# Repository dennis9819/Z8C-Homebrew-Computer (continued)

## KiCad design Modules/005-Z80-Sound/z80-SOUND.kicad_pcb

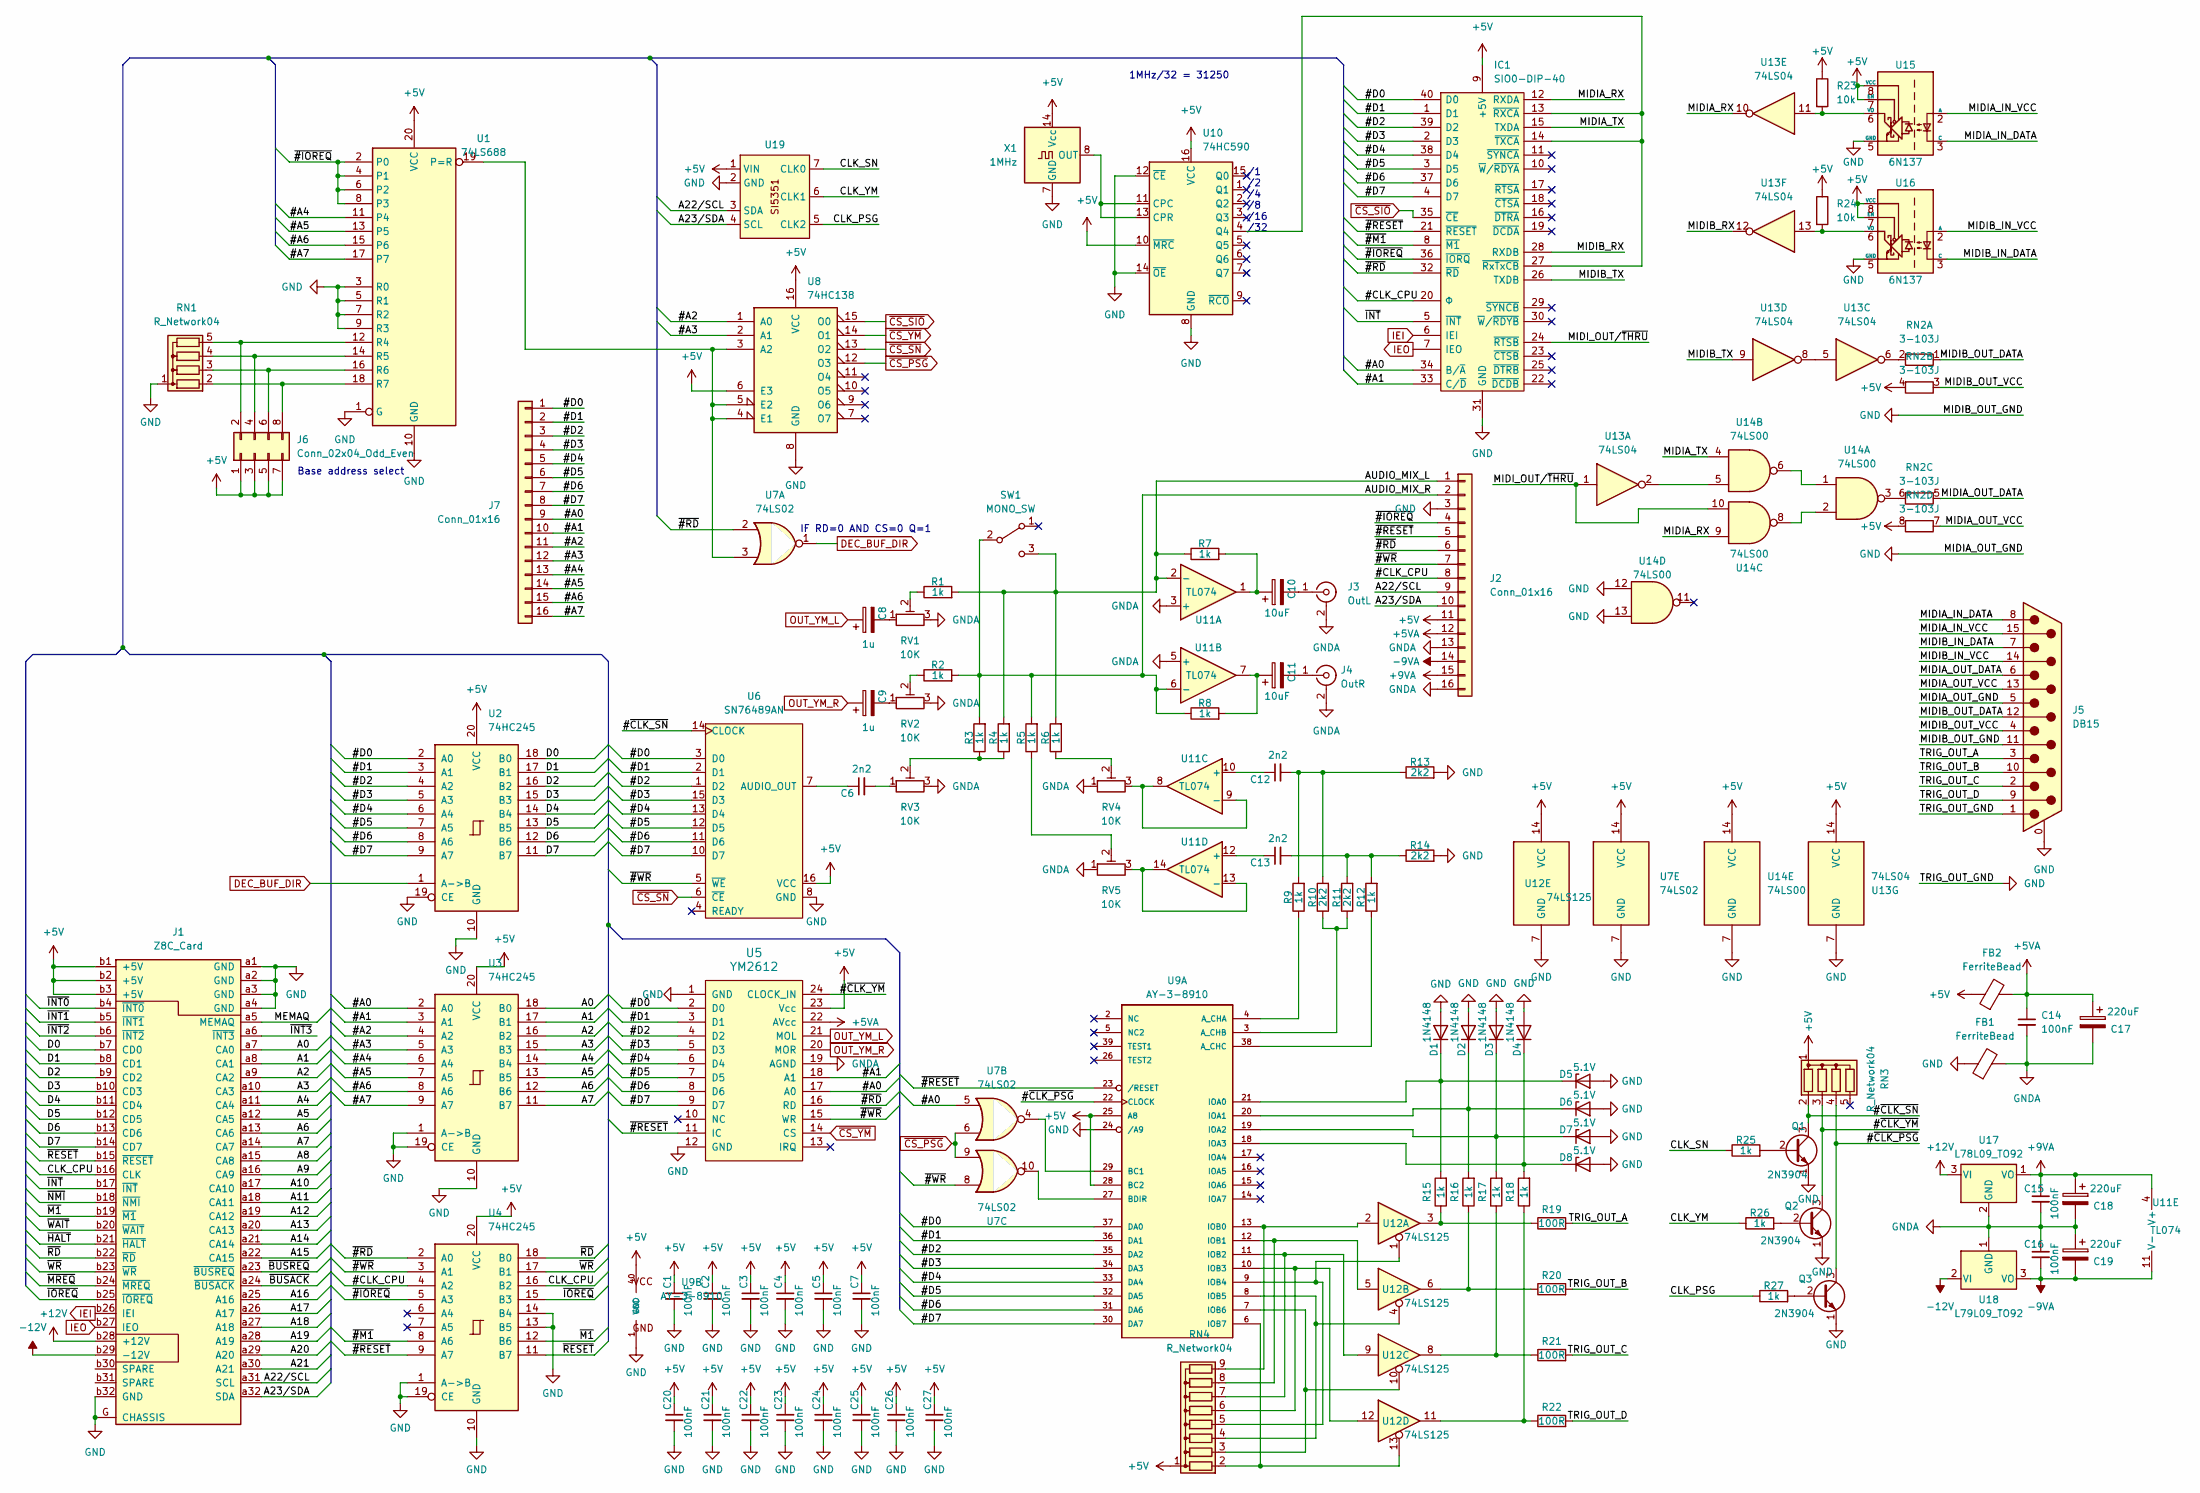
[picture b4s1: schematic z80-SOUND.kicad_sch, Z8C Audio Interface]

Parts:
C1, C2, C3, C4, C5, C7, C14, C15, C16, C20, C21, C22, C23, C24, C25, C26, C27: 100nF; C_Rect_L7.0mm_W2.0mm_P5.00mm
C6, C12, C13: 2n2; C_Rect_L7.0mm_W2.0mm_P5.00mm
C8, C9: 1u; CP_Radial_D6.3mm_P2.50mm
C10, C11: 10uF; CP_Radial_D6.3mm_P2.50mm
C17, C18, C19: 220uF; CP_Radial_D8.0mm_P3.50mm
D1, D2, D3, D4: 1N4148; D_DO-35_SOD27_P7.62mm_Horizontal
D5, D6, D7, D8: 5.1V; D_DO-34_SOD68_P7.62mm_Horizontal
FB1, FB2: FerriteBead; R_Axial_DIN0414_L11.9mm_D4.5mm_P15.24mm_Horizontal
IC1: SIO0-DIP-40; DIP-40_W15.24mm_Socket; Manufacturer_Part_Number Z84C4206PEG; Mouser Part Number 692-Z84C4206PEG
J1: Z8C_Card; Z8C Card
J2, J7: Conn_01x16; PinSocket_1x16_P2.54mm_Vertical
J3: OutL; RCA_Reichelt
J4: OutR; RCA_Reichelt
J5: DB15; DSUB-15_Female_Horizontal_P2.77x2.84mm_EdgePinOffset9.90mm_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
J6: Conn_02x04_Odd_Even; PinHeader_2x04_P2.54mm_Vertical
Q1, Q2, Q3: 2N3904; TO-92_Inline
R1, R2, R3, R4, R5, R6, R7, R8, R9, R12, R15, R16, R17, R18, R25, R26, R27: 1k; R_Axial_DIN0204_L3.6mm_D1.6mm_P7.62mm_Horizontal
R10, R11, R13, R14: 2k2; R_Axial_DIN0204_L3.6mm_D1.6mm_P7.62mm_Horizontal
R19, R20, R21, R22: 100R; R_Axial_DIN0204_L3.6mm_D1.6mm_P7.62mm_Horizontal
R23, R24: 10k; R_Axial_DIN0204_L3.6mm_D1.6mm_P7.62mm_Horizontal
RN1, RN3: R_Network04; R_Array_SIP5
RN2: 3-103J; R_Array_SIP8
RN4: R_Network04; R_Array_SIP9
RV1, RV2, RV3, RV4, RV5: 10K; Potentiometer_Bourns_3299W_Vertical
SW1: MONO_SW; DPDT_Vertical
U1: 74LS688; DIP-20_W7.62mm_Socket_LongPads
U2, U3, U4: 74HC245; DIP-20_W7.62mm_Socket_LongPads
U5: YM2612; DIP-24_W15.24mm_Socket
U6: SN76489AN; DIP-16_W7.62mm_Socket
U7: 74LS02; DIP-14_W7.62mm_Socket
U8: 74HC138; DIP-16_W7.62mm_Socket_LongPads
U9: AY-3-8910; DIP-40_W15.24mm_Socket
U10: 74HC590; DIP-16_W7.62mm_Socket_LongPads
U11: TL074; DIP-14_W7.62mm_Socket
U12: 74LS125; DIP-14_W7.62mm_Socket
U13: 74LS04; DIP-14_W7.62mm_Socket
U14: 74LS00; DIP-14_W7.62mm_Socket
U15, U16: 6N137; DIP-8_W7.62mm
U17: L78L09_TO92; TO-92_Inline
U18: L79L09_TO92; TO-92_Inline
U19: PinSocket_1x07_P2.54mm_Vertical
X1: 1MHz; Oscillator_DIP-14

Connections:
+5V: C1.1, C2.1, C3.1, C4.1, C5.1, C7.1, C20.1, C21.1, C22.1, C23.1, C24.1, C25.1, C26.1, C27.1, FB2.1, IC1.9 (+5V), J1.b1 (+5V), J1.b2 (+5V), J1.b3 (+5V), J2.11, J6.1, J6.3, J6.5, J6.7, R23.1, R24.1, RN2.4 (R2.2), RN2.8 (R4.2), RN3.1 (common), RN4.1 (common), U1.20 (VCC), U2.20 (VCC), U3.20 (VCC), U4.20 (VCC), U5.23 (Vcc), U6.16 (VCC), U7.14 (VCC), U8.6 (E3), U8.16 (VCC), U9.25 (A8), U9.28 (BC2), U9.40 (VCC), U10.10 (~MRC), U10.16 (VCC), U12.14 (VCC), U13.14 (VCC), U14.14 (VCC), U15.7 (EN), U15.8 (VCC), U16.7 (EN), U16.8 (VCC), U19.1 (VIN), X1.14 (Vcc)
+5VA: C14.1, C17.1, FB2.2, J2.12, U5.22 (AVcc)
+9VA: C15.1, C18.1, J2.15, U11.4 (V+), U17.1 (VO)
+12V: J1.b28 (+12V), U17.3 (VI)
-9VA: C16.2, C19.2, J2.14, U11.11 (V-), U18.3 (VO)
-12V: J1.b29 (-12V), U18.2 (VI)
/#A0: IC1.34 (B/~A), J7.9, U3.2 (A0), U5.17 (A0), U7.5
/#A1: IC1.33 (C/~D), J7.10, U3.3 (A1), U5.18 (A1)
/#A2: J7.11, U3.4 (A2), U8.1 (A0)
/#A3: J7.12, U3.5 (A3), U8.2 (A1)
/#A4: J7.13, U1.11 (P4), U3.6 (A4)
/#A5: J7.14, U1.13 (P5), U3.7 (A5)
/#A6: J7.15, U1.15 (P6), U3.8 (A6)
/#A7: J7.16, U1.17 (P7), U3.9 (A7)
/#CLK_CPU: IC1.20 (Φ), J2.8, U4.4 (A2)
/#D0: IC1.40 (D0), J7.1, U2.2 (A0), U5.2 (D0), U6.3 (D0), U9.37 (DA0)
/#D1: IC1.1 (D1), J7.2, U2.3 (A1), U5.3 (D1), U6.2 (D1), U9.36 (DA1)
/#D2: IC1.39 (D2), J7.3, U2.4 (A2), U5.4 (D2), U6.1 (D2), U9.35 (DA2)
/#D3: IC1.2 (D3), J7.4, U2.5 (A3), U5.5 (D3), U6.15 (D3), U9.34 (DA3)
/#D4: IC1.38 (D4), J7.5, U2.6 (A4), U5.6 (D4), U6.13 (D4), U9.33 (DA4)
/#D5: IC1.3 (D5), J7.6, U2.7 (A5), U5.7 (D5), U6.12 (D5), U9.32 (DA5)
/#D6: IC1.37 (D6), J7.7, U2.8 (A6), U5.8 (D6), U6.11 (D6), U9.31 (DA6)
/#D7: IC1.4 (D7), J7.8, U2.9 (A7), U5.9 (D7), U6.10 (D7), U9.30 (DA7)
/#~CLK_PSG: Q3.3 (C), RN3.4 (R3), U9.22 (CLOCK)
/#~CLK_SN: Q1.3 (C), RN3.2 (R1), U6.14 (CLOCK)
/#~CLK_YM: Q2.3 (C), RN3.3 (R2), U5.24 (CLOCK_IN)
/A0: J1.a7 (CA0), U3.18 (B0)
/A1: J1.a8 (CA1), U3.17 (B1)
/A2: J1.a9 (CA2), U3.16 (B2)
/A3: J1.a10 (CA3), U3.15 (B3)
/A4: J1.a11 (CA4), U3.14 (B4)
/A5: J1.a12 (CA5), U3.13 (B5)
/A6: J1.a13 (CA6), U3.12 (B6)
/A7: J1.a14 (CA7), U3.11 (B7)
/A8: J1.a15 (CA8)
/A9: J1.a16 (CA9)
/A10: J1.a17 (CA10)
/A11: J1.a18 (CA11)
/A12: J1.a19 (CA12)
/A13: J1.a20 (CA13)
/A14: J1.a21 (CA14)
/A15: J1.a22 (CA15)
/A16: J1.a25 (A16)
/A17: J1.a26 (A17)
/A18: J1.a27 (A18)
/A19: J1.a28 (A19)
/A20: J1.a29 (A20)
/A21: J1.a30 (A21)
/A22/SCL: J1.a31 (SCL), J2.9, U19.3 (SDA)
/A23/SDA: J1.a32 (SDA), J2.10, U19.4 (SCL)
/AUDIO_MIX_L: J2.1, R1.2, R4.2, R6.2, R7.1, SW1.3 (C), U11.2 (-)
/AUDIO_MIX_R: J2.2, R2.2, R3.2, R5.2, R8.1, SW1.2 (B), U11.6 (-)
/CLK_CPU: J1.b16 (CLK), U4.16 (B2)
/CLK_PSG: R27.1, U19.5 (CLK2)
/CLK_SN: R25.1, U19.7 (CLK0)
/CLK_YM: R26.1, U19.6 (CLK1)
/D0: J1.b7 (CD0), U2.18 (B0)
/D1: J1.b8 (CD1), U2.17 (B1)
/D2: J1.b9 (CD2), U2.16 (B2)
/D3: J1.b10 (CD3), U2.15 (B3)
/D4: J1.b11 (CD4), U2.14 (B4)
/D5: J1.b12 (CD5), U2.13 (B5)
/D6: J1.b13 (CD6), U2.12 (B6)
/D7: J1.b14 (CD7), U2.11 (B7)
/MEMAQ: J1.a5 (MEMAQ)
/MIDIA_IN_DATA: J5.8, U15.3 (C)
/MIDIA_IN_VCC: J5.15, U15.2 (A)
/MIDIA_OUT_DATA: J5.6, RN2.5 (R3.1)
/MIDIA_OUT_VCC: J5.13, RN2.7 (R4.1)
/MIDIA_RX: IC1.12 (RXDA), U13.10, U14.9
/MIDIA_TX: IC1.15 (TXDA), U14.4
/MIDIB_IN_DATA: J5.7, U16.3 (C)
/MIDIB_IN_VCC: J5.14, U16.2 (A)
/MIDIB_OUT_DATA: J5.12, RN2.1 (R1.1)
/MIDIB_OUT_VCC: J5.4, RN2.3 (R2.1)
/MIDIB_RX: IC1.28 (RXDB), U13.12
/MIDIB_TX: IC1.26 (TXDB), U13.9
/MIDI_OUT/~THRU: IC1.24 (~RTSB), U13.1, U14.10
/TRIG_OUT_A: J5.3, R19.2
/TRIG_OUT_B: J5.10, R20.2
/TRIG_OUT_C: J5.2, R21.2
/TRIG_OUT_D: J5.9, R22.2
/~#IOREQ: IC1.36 (~IORQ), J2.4, U1.2 (P0), U1.4 (P1), U1.6 (P2), U1.8 (P3), U4.5 (A3)
/~#M1: IC1.8 (~M1), U4.8 (A6)
/~#RD: IC1.32 (~RD), J2.6, U4.2 (A0), U5.16 (RD), U7.2
/~#RESET: IC1.21 (~RESET), J2.5, U4.9 (A7), U5.11 (IC), U9.23 (/RESET)
/~#WR: J2.7, U4.3 (A1), U5.15 (WR), U6.5 (~WE), U7.8
/~BUSACK: J1.a24 (~BUSACK)
/~BUSREQ: J1.a23 (~BUSREQ)
/~HALT: J1.b21 (~HALT)
/~INT0: J1.b4 (~INT0)
/~INT1: J1.b5 (~INT1)
/~INT2: J1.b6 (~INT2)
/~INT3: J1.a6 (~INT3)
/~INT: IC1.5 (~INT), J1.b17 (~INT)
/~IOREQ: J1.b25 (~IOREQ), U4.15 (B3)
/~M1: J1.b19 (~M1), U4.12 (B6)
/~MREQ: J1.b24 (~MREQ)
/~NMI: J1.b18 (~NMI)
/~RD: J1.b22 (~RD), U4.18 (B0)
/~RESET: J1.b15 (~RESET), U4.11 (B7)
/~WAIT: J1.b20 (~WAIT)
/~WR: J1.b23 (~WR), U4.17 (B1)
DEC_BUF_DIR: U2.1 (A->B), U7.1
GND: C1.2, C2.2, C3.2, C4.2, C5.2, C7.2, C20.2, C21.2, C22.2, C23.2, C24.2, C25.2, C26.2, C27.2, D1.2 (A), D2.2 (A), D3.2 (A), D4.2 (A), D5.2 (A), D6.2 (A), D7.2 (A), D8.2 (A), FB1.1, IC1.31 (GND), J1.G (CHASSIS), J1.a1 (GND), J1.a2 (GND), J1.a3 (GND), J1.a4 (GND), J1.b32 (GND), J2.3, J5.0 (PAD), J5.1, J5.5, J5.11 (P111), Q1.1 (E), Q2.1 (E), Q3.1 (E), R13.2, R14.2, RN1.1 (common), U1.1 (G), U1.3 (R0), U1.5 (R1), U1.7 (R2), U1.9 (R3), U1.10 (GND), U2.10 (GND), U2.19 (CE), U3.1 (A->B), U3.10 (GND), U3.19 (CE), U4.1 (A->B), U4.10 (GND), U4.13 (B5), U4.14 (B4), U4.19 (CE), U5.1 (GND), U5.12 (GND), U6.8 (GND), U7.7 (GND), U8.8 (GND), U9.1 (GND), U9.24 (/A9), U10.8 (GND), U10.12 (~CE), U10.14 (~OE), U12.7 (GND), U13.7 (GND), U14.7 (GND), U14.12, U14.13, U15.5 (GND), U16.5 (GND), U19.2 (GND), X1.7 (GND)
GNDA: C14.2, C15.2, C16.1, C17.2, C18.2, C19.1, FB1.2, J2.13, J2.16, J3.2 (Ext), J4.2 (Ext), RV1.3, RV2.3, RV3.3, RV4.1, RV5.1, U5.19 (AGND), U11.3 (+), U11.5 (+), U17.2 (GND), U18.1 (GND)
IEI: IC1.6 (IEI), J1.b26 (IEI)
IEO: IC1.7 (IEO), J1.b27 (IEO)
unnamed: C6.2, RV3.1
unnamed: C8.2, RV1.1
unnamed: C9.2, RV2.1
unnamed: C10.1, R7.2, U11.1
unnamed: C11.1, R8.2, U11.7
unnamed: C12.2, R9.2, R10.2, R13.1
unnamed: C13.2, R11.2, R12.2, R14.1
unnamed: D1.1 (K), D5.1 (K), R15.2, U9.21 (IOA0)
unnamed: D2.1 (K), D6.1 (K), R16.2, U9.20 (IOA1)
unnamed: D3.1 (K), D7.1 (K), R17.2, U9.19 (IOA2)
unnamed: D4.1 (K), D8.1 (K), R18.2, U9.18 (IOA3)
unnamed: IC1.13 (~RXCA), IC1.14 (~TXCA), IC1.27 (~RxTxCB), U10.4 (Q4)
unnamed: C10.2, J3.1 (In)
unnamed: C11.2, J4.1 (In)
unnamed: J6.2, RN1.5 (R4), U1.12 (R4)
unnamed: J6.4, RN1.4 (R3), U1.14 (R5)
unnamed: J6.6, RN1.3 (R2), U1.16 (R6)
unnamed: J6.8, RN1.2 (R1), U1.18 (R7)
unnamed: Q1.2 (B), R25.2
unnamed: Q2.2 (B), R26.2
unnamed: Q3.2 (B), R27.2
unnamed: R1.1, RV1.2
unnamed: R2.1, RV2.2
unnamed: R3.1, R4.1, RV3.2
unnamed: R5.1, RV5.2
unnamed: R6.1, RV4.2
unnamed: R15.1, R19.1, U12.3
unnamed: R16.1, R20.1, U12.6
unnamed: R17.1, R21.1, U12.8
unnamed: R18.1, R22.1, U12.11
unnamed: RN2.2 (R1.2), U13.6
unnamed: RN2.6 (R3.2), U14.3
unnamed: RN4.2 (R1), U9.6 (IOB7), U12.13
unnamed: RN4.3 (R2), U9.7 (IOB6), U12.10
unnamed: RN4.4 (R3), U9.8 (IOB5), U12.4
unnamed: RN4.5 (R4), U9.9 (IOB4), U12.1
unnamed: RN4.6 (R5), U9.10 (IOB3), U12.12
unnamed: RN4.7 (R6), U9.11 (IOB2), U12.9
unnamed: RN4.8 (R7), U9.12 (IOB1), U12.5
unnamed: RN4.9 (R8), U9.13 (IOB0), U12.2
unnamed: U1.19 (P=R), U7.3, U8.3 (A2), U8.4 (E1), U8.5 (E2)
unnamed: C6.1, U6.7 (AUDIO_OUT)
unnamed: R9.1, U9.4 (A_CHA)
unnamed: R10.1, R11.1, U9.3 (A_CHB)
unnamed: R12.1, U9.38 (A_CHC)
unnamed: U7.4, U9.29 (BC1)
unnamed: U7.10, U9.27 (BDIR)
unnamed: U10.11 (CPC), U10.13 (CPR), X1.8 (OUT)
unnamed: C12.1, U11.10 (+)
unnamed: RV4.3, U11.8, U11.9 (-)
unnamed: C13.1, U11.12 (+)
unnamed: RV5.3, U11.13 (-), U11.14
unnamed: U13.2, U14.5
unnamed: U13.5, U13.8
unnamed: U14.1, U14.6
unnamed: U14.2, U14.8
unnamed: R23.2, U13.11, U15.6 (VO)
unnamed: R24.2, U13.13, U16.6 (VO)
OUT_YM_L: C8.1, U5.21 (MOL)
OUT_YM_R: C9.1, U5.20 (MOR)
~CS_PSG: U7.6, U7.9, U8.12 (O3)
~CS_SIO: IC1.35 (~CE), U8.15 (O0)
~CS_SN: U6.6 (~CE), U8.13 (O2)
~CS_YM: U5.14 (CS), U8.14 (O1)

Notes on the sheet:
/1 /2 /4 /8 /16 /32
Base address select
IF RD=0 AND CS=0 Q=1
1MHz/32 = 31250

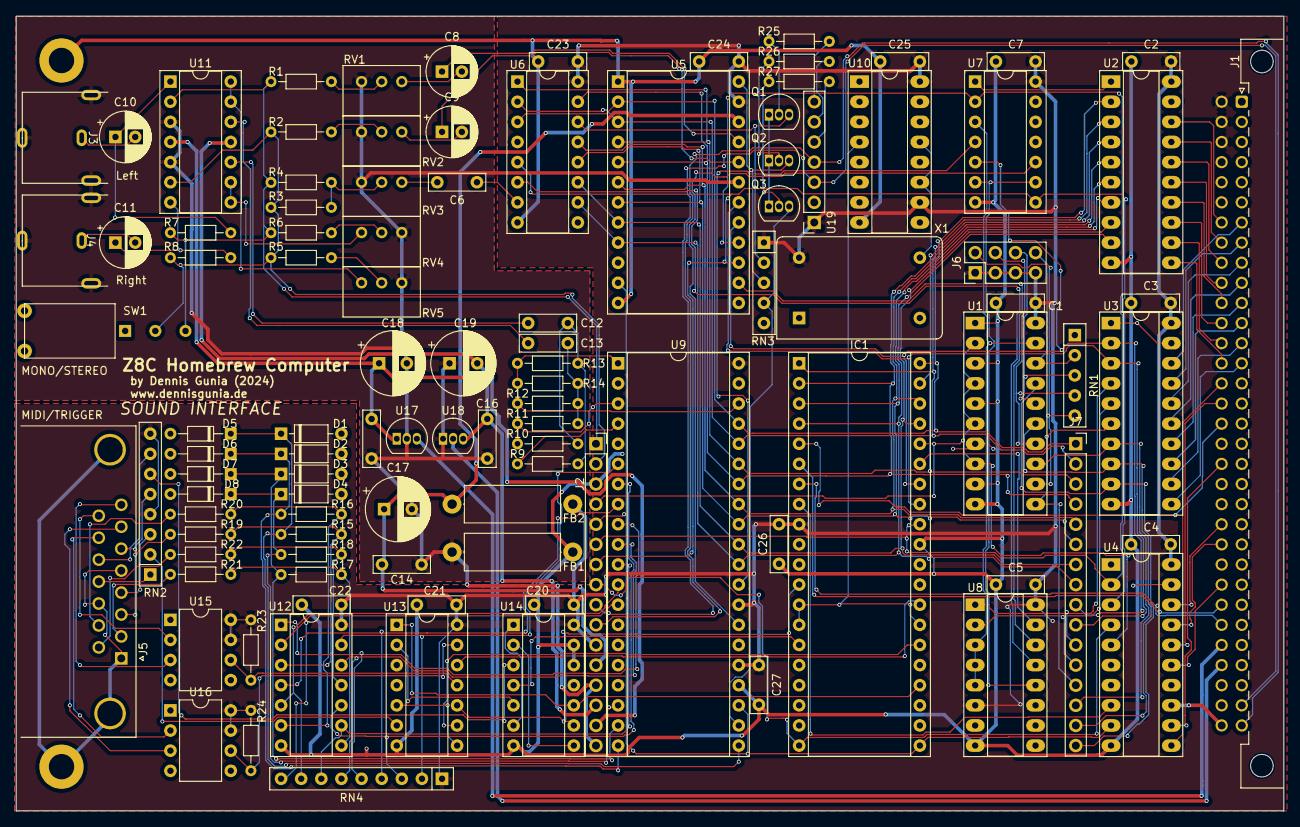
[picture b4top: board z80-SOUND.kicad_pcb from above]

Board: 2 copper layers, 160.0 x 100.3 mm, 105 parts (0 on the bottom side), 147 nets.

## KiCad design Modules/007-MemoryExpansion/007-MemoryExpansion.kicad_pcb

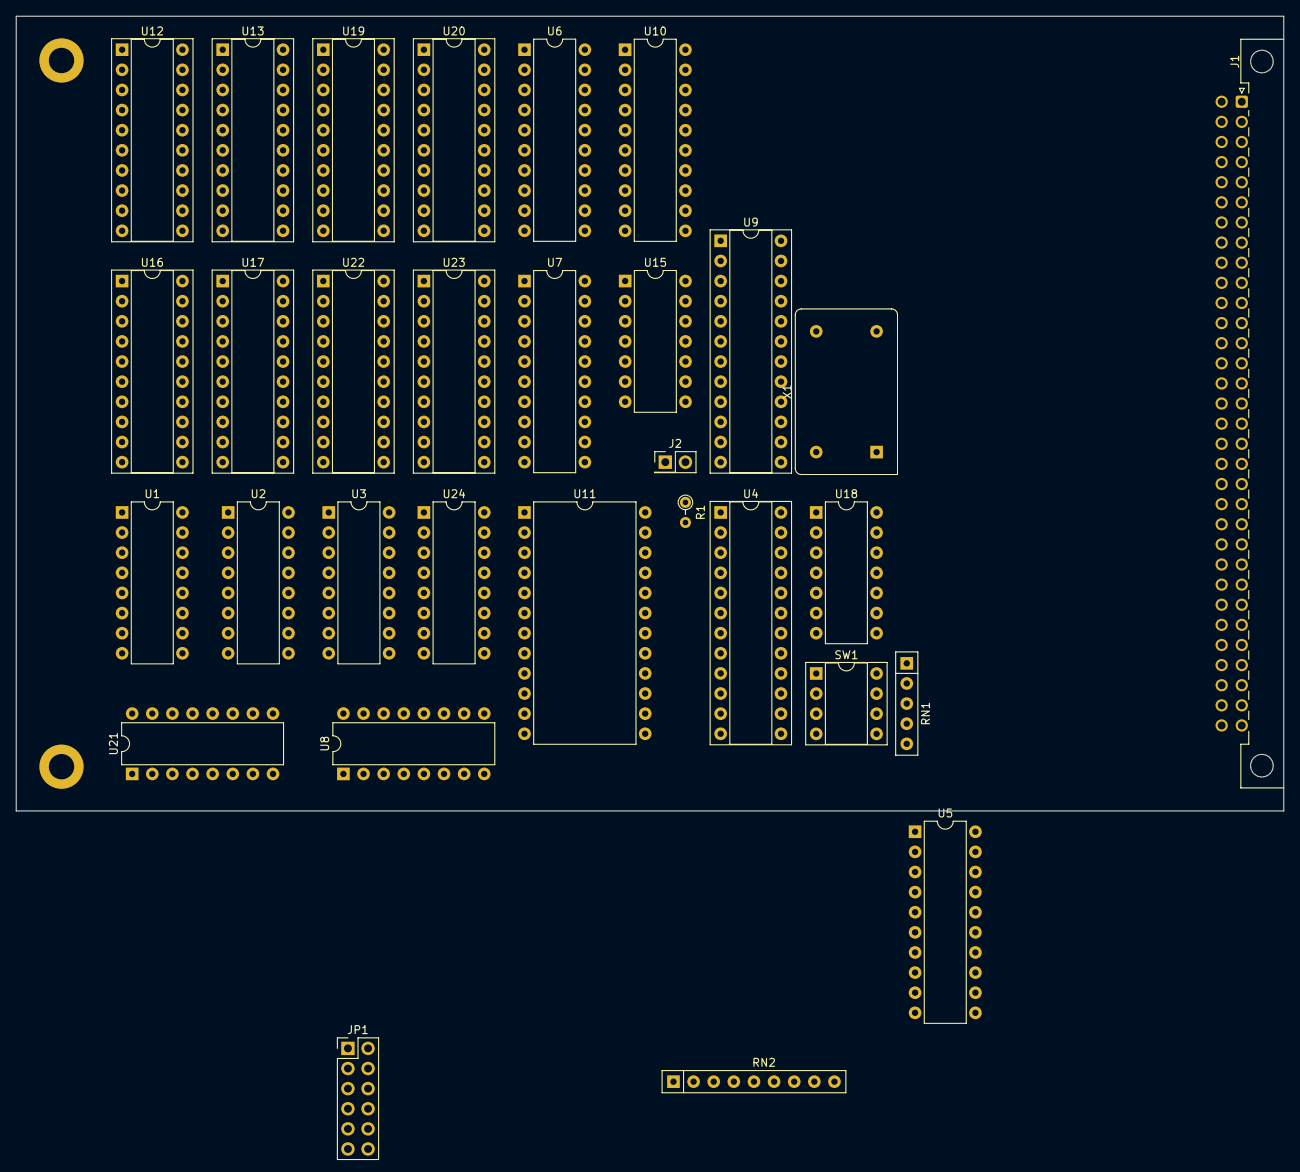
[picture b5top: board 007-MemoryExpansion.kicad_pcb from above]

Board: 2 copper layers, 160.0 x 100.3 mm, 31 parts (0 on the bottom side), 98 nets, no tracks yet.

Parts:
J1: Z8C_Ca#RD; Z8C Card
J2: ENA19; PinHeader_2x01_P2.54mm_Vertical
JP1: Conn_02x06_Odd_Even; PinHeader_2x06_P2.54mm_Vertical
R1: 4.7k; R_Axial_DIN0204_L3.6mm_D1.6mm_P2.54mm_Vertical
RN1: 4k7; R_Array_SIP5
RN2: R_Network08; R_Array_SIP9
SW1: SW_DIP_x04; DIP-8_W7.62mm_Socket
U1, U2, U3, U8: 74LS157; DIP-16_W7.62mm
U4, U9: DIP-24_W7.62mm_Socket
U5: 74LS688; DIP-20_W7.62mm
U6, U10: 74LS245; DIP-20_W7.62mm
U7: 74LS374; DIP-20_W7.62mm
U11: DIP-24_W15.24mm
U12, U13, U16, U17, U19, U20, U22, U23: DIP-20_W7.62mm_Socket
U15: 74LS74; DIP-14_W7.62mm
U18: 74LS125; DIP-14_W7.62mm
U21: 74LS138; DIP-16_W7.62mm
U24: 74LS175; DIP-16_W7.62mm
X1: 40MHz; Oscillator_DIP-14

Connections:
+5V: J1.b1 (+5V), J1.b2 (+5V), J1.b3 (+5V), J2.1, JP1.1, JP1.3, JP1.5, JP1.7, JP1.9, JP1.11, SW1.1, SW1.2, SW1.3, SW1.4, U4.24 (VCC), U5.20 (VCC), U6.20 (VCC), U7.20 (VCC), U8.16 (VCC), U9.24 (VCC), U10.20 (VCC), U11.24 (Vcc), U12.20 (VSS), U13.20 (VSS), U16.20 (VSS), U17.20 (VSS), U19.20 (VSS), U20.20 (VSS), U21.6 (E3), U21.16 (VCC), U22.20 (VSS), U23.20 (VSS), U24.1 (~Mr), U24.16 (VCC), X1.14 (Vcc)
/#CA0: U1.2 (I0a), U4.9 (I9)
/#CA1: U1.5 (I0b), U4.11 (I10)
/#CA2: U1.11 (I0c), U5.6 (P2)
/#CA3: U1.14 (I0d), U5.8 (P3)
/#CA4: U2.2 (I0a), U5.11 (P4)
/#CA5: U2.5 (I0b), U5.13 (P5)
/#CA6: U2.11 (I0c), U5.15 (P6)
/#CA7: U2.14 (I0d), U5.17 (P7)
/#CA15: U4.13 (I13/~OE), U8.13 (I1d)
/#CD0: U6.2 (A0), U7.3 (D0), U10.2 (A0), U18.3, U24.4 (D0)
/#CD1: U6.3 (A1), U7.4 (D1), U10.3 (A1), U24.5 (D1)
/#CD2: U6.4 (A2), U7.7 (D2), U10.4 (A2), U24.12 (D2)
/#CD3: U6.5 (A3), U7.8 (D3), U10.5 (A3), U24.13 (D3)
/#CD4: U6.6 (A4), U7.13 (D4), U10.6 (A4)
/#CD5: U6.7 (A5), U7.14 (D5), U10.7 (A5)
/#CD6: U6.8 (A6), U7.17 (D6), U10.8 (A6)
/#CD7: U6.9 (A7), U7.18 (D7), U10.9 (A7)
/JENA19: J2.2, R1.1, U18.2
/MBA12: U1.13 (I1d), U10.18 (B0), U11.9 (D0)
/MBA13: U2.3 (I1a), U10.17 (B1), U11.10 (D1)
/MBA14: U2.6 (I1b), U10.16 (B2), U11.11 (D2)
/MBA15: U2.10 (I1c), U10.15 (B3), U11.13 (D3)
/MBA16: U2.13 (I1d), U10.14 (B4), U11.14 (D4)
/MBA17: U3.3 (I1a), U10.13 (B5), U11.15 (D5)
/MBA18: U10.12 (B6), U11.16 (D6), U21.1 (A0)
/MBPROT: U4.16 (IO16), U10.11 (B7), U11.17 (D7)
/MDA0: U6.18 (B0), U12.1 (DQ0), U13.1 (DQ0), U19.1 (DQ0), U20.1 (DQ0)
/MDA1: U6.17 (B1), U12.2 (DQ1), U13.2 (DQ1), U19.2 (DQ1), U20.2 (DQ1)
/MDA2: U6.16 (B2), U12.18 (DQ2), U13.18 (DQ2), U19.18 (DQ2), U20.18 (DQ2)
/MDA3: U6.15 (B3), U12.19 (DQ3), U13.19 (DQ3), U19.19 (DQ3), U20.19 (DQ3)
/MDA4: U6.14 (B4), U16.1 (DQ0), U17.1 (DQ0), U22.1 (DQ0), U23.1 (DQ0)
/MDA5: U6.13 (B5), U16.2 (DQ1), U17.2 (DQ1), U22.2 (DQ1), U23.2 (DQ1)
/MDA6: U6.12 (B6), U16.18 (DQ2), U17.18 (DQ2), U22.18 (DQ2), U23.18 (DQ2)
/MDA7: U6.11 (B7), U16.19 (DQ3), U17.19 (DQ3), U22.19 (DQ3), U23.19 (DQ3)
/MMA0: U1.4 (Za), U12.6 (A0), U13.6 (A0), U16.6 (A0), U17.6 (A0), U19.6 (A0), U20.6 (A0), U22.6 (A0), U23.6 (A0)
/MMA1: U1.7 (Zb), U12.7 (A1), U13.7 (A1), U16.7 (A1), U17.7 (A1), U19.7 (A1), U20.7 (A1), U22.7 (A1), U23.7 (A1)
/MMA2: U1.9 (Zc), U12.8 (A2), U13.8 (A2), U16.8 (A2), U17.8 (A2), U19.8 (A2), U20.8 (A2), U22.8 (A2), U23.8 (A2)
/MMA3: U1.12 (Zd), U12.9 (A3), U13.9 (A3), U16.9 (A3), U17.9 (A3), U19.9 (A3), U20.9 (A3), U22.9 (A3), U23.9 (A3)
/MMA4: U2.4 (Za), U12.11 (A4), U13.11 (A4), U16.11 (A4), U17.11 (A4), U19.11 (A4), U20.11 (A4), U22.11 (A4), U23.11 (A4)
/MMA5: U2.7 (Zb), U12.12 (A5), U13.12 (A5), U16.12 (A5), U17.12 (A5), U19.12 (A5), U20.12 (A5), U22.12 (A5), U23.12 (A5)
/MMA6: U2.9 (Zc), U12.13 (A6), U13.13 (A6), U16.13 (A6), U17.13 (A6), U19.13 (A6), U20.13 (A6), U22.13 (A6), U23.13 (A6)
/MMA7: U2.12 (Zd), U12.14 (A7), U13.14 (A7), U16.14 (A7), U17.14 (A7), U19.14 (A7), U20.14 (A7), U22.14 (A7), U23.14 (A7)
/MMA8: U3.4 (Za), U12.15 (A8), U13.15 (A8), U16.15 (A8), U17.15 (A8), U19.15 (A8), U20.15 (A8), U22.15 (A8), U23.15 (A8)
/MPROTEN: U4.15 (IO15), U7.19 (O7)
/MUXEN: U1.15 (E), U2.15 (E), U3.15 (E), U9.17 (IO17)
/REGBNK0: U7.2 (O0), U11.4 (A4)
/REGBNK1: U7.5 (O1), U11.3 (A5)
/REGBNK2: U7.6 (O2), U11.2 (A6)
/REGBNK3: U7.9 (O3), U11.1 (A7)
/REGBNK4: U7.12 (O4), U11.23 (A8)
/REGBNK5: U7.15 (O5), U11.22 (A9)
/REGBNK6: U7.16 (O6), U11.19 (A10)
/REGMAP0: U8.2 (I0a), U24.2 (Q0)
/REGMAP1: U8.5 (I0b), U24.7 (Q1)
/REGMAP2: U8.11 (I0c), U24.10 (Q2)
/REGMAP3: U8.14 (I0d), U24.15 (Q3)
/WRPROT: U4.19 (IO19), U7.11 (Cp)
/WRREG: U4.22 (IO22), U24.9 (Cp)
/~#DRAMREQ: U4.23 (IO23), U6.19 (CE), U9.6 (I6), U21.4 (E1)
/~#MREQ: U4.6 (I6), U9.7 (I7)
/~#RD: U4.7 (I7), U9.8 (I8)
/~#WR: U4.8 (I8), U6.1 (A->B), U9.9 (I9), U10.1 (A->B), U21.3 (A2)
/~CARDSEL: U4.5 (I5), U5.19 (P=R)
/~CSMAP: U4.20 (IO20), U8.1 (S), U10.19 (CE)
/~DBANK1_RD: U12.16 (~OE), U16.16 (~OE), U21.11 (O4)
/~DBANK1_WR: U12.3 (~WE), U16.3 (~WE), U21.15 (O0)
/~DBANK2_RD: U13.16 (~OE), U17.16 (~OE), U21.10 (O5)
/~DBANK2_WR: U13.3 (~WE), U17.3 (~WE), U21.14 (O1)
/~DBANK3_RD: U19.16 (~OE), U21.9 (O6), U22.16 (~OE)
/~DBANK3_WR: U19.3 (~WE), U21.13 (O2), U22.3 (~WE)
/~DBANK4_RD: U20.16 (~OE), U21.7 (O7), U23.16 (~OE)
/~DBANK4_WR: U20.3 (~WE), U21.12 (O3), U23.3 (~WE)
/~ENRAMDEC: U9.23 (IO23), U21.5 (E2)
/~MCAS: U9.15 (IO15), U12.17 (~CAS), U13.17 (~CAS), U16.17 (~CAS), U17.17 (~CAS), U19.17 (~CAS), U20.17 (~CAS), U22.17 (~CAS), U23.17 (~CAS)
/~MMUX: U1.1 (S), U2.1 (S), U3.1 (S), U9.16 (IO16)
/~MRAS: U9.14 (IO14), U12.4 (~RAS), U13.4 (~RAS), U16.4 (~RAS), U17.4 (~RAS), U19.4 (~RAS), U20.4 (~RAS), U22.4 (~RAS), U23.4 (~RAS)
/~NMIGAT: U4.14 (IO14), U18.4
/~RDPROT: U4.18 (IO18), U18.1
/~WRMAP: U4.21 (IO21), U11.21 (R/~W)
GND: J1.a1 (GND), J1.a2 (GND), J1.a3 (GND), J1.a4 (GND), J1.b32 (GND), R1.2, RN1.1 (common), RN2.1 (common), U4.12 (GND), U5.1 (G), U5.2 (P0), U5.10 (GND), U6.10 (GND), U7.1 (OE), U7.10 (GND), U8.8 (GND), U8.15 (E), U9.12 (GND), U9.13 (I13/~OE), U10.10 (GND), U11.12 (GND), U11.18 (~CS), U11.20 (~OE), U12.10 (VCC), U13.10 (VCC), U16.10 (VCC), U17.10 (VCC), U18.5, U19.10 (VCC), U20.10 (VCC), U21.8 (GND), U22.10 (VCC), U23.10 (VCC), U24.8 (GND), X1.7 (GND)
unnamed: JP1.2, RN2.7 (R6), U5.7 (R2)
unnamed: JP1.4, RN2.6 (R5), U5.9 (R3)
unnamed: JP1.6, RN2.5 (R4), U5.12 (R4)
unnamed: JP1.8, RN2.4 (R3), U5.14 (R5)
unnamed: JP1.10, RN2.3 (R2), U5.16 (R6)
unnamed: JP1.12, RN2.2 (R1), U5.18 (R7)
unnamed: RN1.2 (R1), SW1.8, U4.4 (I4)
unnamed: RN1.3 (R2), SW1.7, U4.3 (I3)
unnamed: RN1.4 (R3), SW1.6, U4.2 (I2)
unnamed: RN1.5 (R4), SW1.5, U4.1 (I1/CLK)
unnamed: RN2.8 (R7), U5.5 (R1)
unnamed: RN2.9 (R8), U5.3 (R0)
unnamed: U9.1 (I1/CLK), X1.8 (OUT)
unnamed: U8.4 (Za), U11.8 (A0)
unnamed: U8.7 (Zb), U11.7 (A1)
unnamed: U8.9 (Zc), U11.6 (A2)
unnamed: U8.12 (Zd), U11.5 (A3)

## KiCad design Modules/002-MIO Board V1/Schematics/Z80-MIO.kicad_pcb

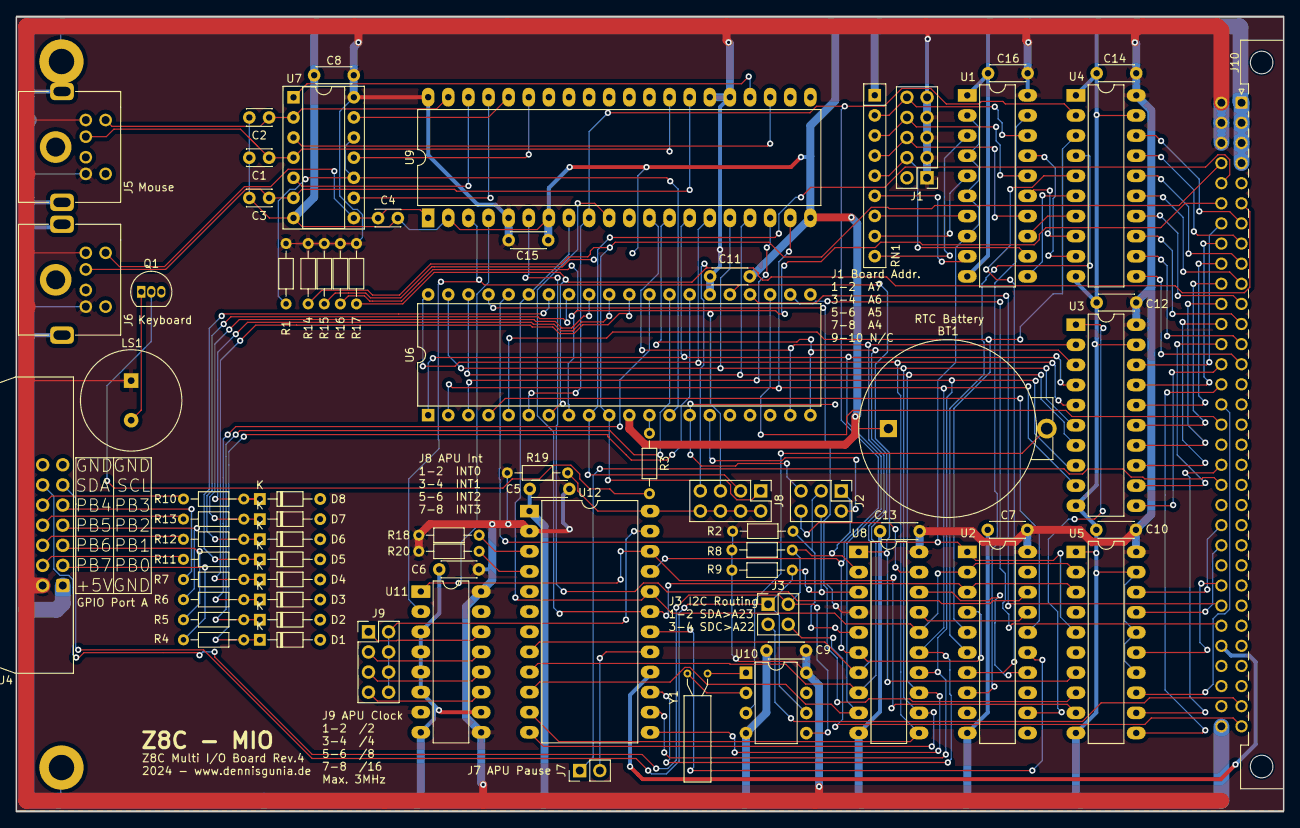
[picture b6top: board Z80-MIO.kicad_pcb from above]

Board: 2 copper layers, 160.0 x 100.3 mm, 71 parts (0 on the bottom side), 120 nets.

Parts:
BT1: 3V; Battery_Holder_Coin_2032_BS-7
C1, C2, C3, C4: 47pF; C_Disc_D3.0mm_W2.0mm_P2.50mm
C5, C6, C7, C8, C9, C10, C11, C12, C13, C14, C15, C16: 100nF; C_Disc_D4.3mm_W1.9mm_P5.00mm
D1, D2, D3, D4, D5, D6, D7, D8: 5.1V; D_DO-34_SOD68_P7.62mm_Horizontal
J1: Conn_02x05_Odd_Even; PinHeader_2x05_P2.54mm_Vertical
J2: Conn_02x02_Top_Bottom; PinHeader_2x03_P2.54mm_Vertical
J3: Conn_02x02_Top_Bottom; PinHeader_2x02_P2.54mm_Vertical
J4: Conn_02x07_Odd_Even; IDC-Header_2x07_P2.54mm_Latch_Horizontal
J5, J6: Mini-DIN-6; PS2
J7: Jumper_2_Bridged; PinHeader_1x02_P2.54mm_Vertical
J8, J9: Conn_02x04_Odd_Even; PinHeader_2x04_P2.54mm_Vertical
J10: Z8C_Card; Z8C Card
LS1: Speaker; Piezo_Transducer_THT_PS1240P02BT
Q1: BC548; TO-92_Inline
R1, R8, R9, R14, R15, R16, R17, R19: 4k7; R_Axial_DIN0204_L3.6mm_D1.6mm_P7.62mm_Horizontal
R2, R18, R20: 10k; R_Axial_DIN0204_L3.6mm_D1.6mm_P7.62mm_Horizontal
R3: 220; R_Axial_DIN0204_L3.6mm_D1.6mm_P7.62mm_Horizontal
R4, R5, R6, R7, R10, R11, R12, R13: 68; R_Axial_DIN0204_L3.6mm_D1.6mm_P7.62mm_Horizontal
RN1: R_Network08; R_Array_SIP9
U1: 74HC688; DIP-20_W7.62mm_LongPads
U2: GAL16V8; DIP-20_W7.62mm_LongPads
U3: 74HC2T45; DIP-20_W7.62mm_LongPads
U4, U5: 74HC245; DIP-20_W7.62mm_LongPads
U6: PIO-DIP-40; DIP-40_W15.24mm
U7: 7406; DIP-14_W7.62mm_Socket
U8: PCF8584; DIP-20_W7.62mm_LongPads
U9: 8048; DIP-40_W15.24mm_LongPads
U10: DS1307+; DIP-8_W7.62mm
U11: 74HC161; DIP-16_W7.62mm_LongPads
U12: Am9511A; DIP-24_W15.24mm_LongPads
Y1: 32.768 kHz; Crystal_AT310_D3.0mm_L10.0mm_Horizontal

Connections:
+5V: C5.1, C6.1, C7.1, C8.1, C9.1, C10.1, C11.1, C12.1, C13.1, C14.1, C15.1, C16.1, J1.1, J1.3, J1.5, J1.7, J1.9, J4.2, J5.4, J6.4, J10.b1 (+5V), J10.b2 (+5V), J10.b3 (+5V), LS1.1, R1.1, R2.1, R8.1, R9.1, R14.2, R15.2, R16.2, R17.2, R18.1, R19.1, R20.1, U1.20 (VCC), U2.20 (VCC), U3.20 (VCC), U4.20 (VCC), U5.20 (VCC), U6.26 (VCC), U7.14 (VCC), U8.4 (~IACK), U8.20 (VDD), U9.5 (~SS), U9.25 (PROG), U9.26 (VDD), U9.40 (VCC), U10.8 (VCC), U11.7 (CEP), U11.9 (~PE), U11.16 (VCC), U12.2 (VCC)
+12V: J10.b28 (+12V), U12.16 (VDD)
/#A0: U2.4 (I4), U4.2 (A0), U6.6 (B/~A), U8.6 (A0), U9.9 (~PSEN), U12.21 (C/~D)
/#A1: U2.5 (I5), U4.3 (A1), U6.5 (C/~D)
/#A2: U2.6 (I6), U4.4 (A2)
/#A3: U2.7 (I7), U4.5 (A3)
/#A4: U1.11 (P4), U4.6 (A4)
/#A5: U1.13 (P5), U4.7 (A5)
/#A6: U1.15 (P6), U4.8 (A6)
/#A7: U1.17 (P7), U4.9 (A7)
/#CLK_CPU: U5.7 (A5), U6.25 (CLK), U8.1 (CLK), U9.3 (X2), U11.2 (CP)
/#D0: U3.2 (A0), U6.19 (D0), U8.7 (D0), U9.12 (DB.0), U12.8 (D0)
/#D1: U3.3 (A1), U6.20 (D1), U8.8 (D1), U9.13 (DB.1), U12.9 (D1)
/#D2: U3.4 (A2), U6.1 (D2), U8.9 (D2), U9.14 (DB.2), U12.10 (D2)
/#D3: U3.5 (A3), U6.40 (D3), U8.11 (D3), U9.15 (DB.3), U12.11 (D3)
/#D4: U3.6 (A4), U6.39 (D4), U8.12 (D4), U9.16 (DB.4), U12.12 (D4)
/#D5: U3.7 (A5), U6.38 (D5), U8.13 (D5), U9.17 (DB.5), U12.13 (D5)
/#D6: U3.8 (A6), U6.3 (D6), U8.14 (D6), U9.18 (DB.6), U12.14 (D6)
/#D7: U3.9 (A7), U6.2 (D7), U8.15 (D7), U9.19 (DB.7), U12.15 (D7)
/A0: J10.a7 (CA0), U4.18 (B0)
/A1: J10.a8 (CA1), U4.17 (B1)
/A2: J10.a9 (CA2), U4.16 (B2)
/A3: J10.a10 (CA3), U4.15 (B3)
/A4: J10.a11 (CA4), U4.14 (B4)
/A5: J10.a12 (CA5), U4.13 (B5)
/A6: J10.a13 (CA6), U4.12 (B6)
/A7: J10.a14 (CA7), U4.11 (B7)
/A22/SCL: J3.3, J10.a31 (SCL)
/A23/SDA: J3.4, J10.a32 (SDA)
/CLK_CPU: J10.b16 (CLK), U5.13 (B5)
/D0: J10.b7 (CD0), U3.18 (B0)
/D1: J10.b8 (CD1), U3.17 (B1)
/D2: J10.b9 (CD2), U3.16 (B2)
/D3: J10.b10 (CD3), U3.15 (B3)
/D4: J10.b11 (CD4), U3.14 (B4)
/D5: J10.b12 (CD5), U3.13 (B5)
/D6: J10.b13 (CD6), U3.12 (B6)
/D7: J10.b14 (CD7), U3.11 (B7)
/FPU_CLK: J9.2, J9.4, J9.6, J9.8, U12.23 (CLK)
/I2C_SCL: J2.4, J3.1, J4.11, R9.2, U8.3 (SCL), U10.6 (SCL)
/I2C_SDA: J2.1, J3.2, J4.12, R8.2, U8.2 (SDA), U10.5 (SDA)
/PIO_PA0: J2.2, U6.15 (PA0)
/PIO_PA1: J2.5, U6.14 (PA1)
/PIO_PB0: J4.3, R4.2
/PIO_PB1: J4.5, R5.2
/PIO_PB2: J4.7, R6.2
/PIO_PB3: J4.9, R7.2
/PIO_PB4: J4.10, R10.2
/PIO_PB5: J4.8, R13.2
/PIO_PB6: J4.6, R12.2
/PIO_PB7: J4.4, R11.2
/SPK_DRV: R3.1, U6.12 (PA3)
/~#IOREQ: U1.2 (P0), U1.4 (P1), U1.6 (P2), U1.8 (P3), U2.1 (I1/CLK), U5.5 (A3), U6.36 (~IORQ)
/~#M1: U5.8 (A6), U6.37 (~M1)
/~#RD: U2.2 (I2), U5.2 (A0), U6.35 (~RD), U8.16 (~RD), U9.8 (~RD), U12.20 (~RD)
/~#RESET: U5.9 (A7), U9.4 (~RESET), U11.1 (~MR), U12.22 (RESET)
/~#WR: U2.3 (I3), U5.3 (A1), U9.10 (~WR), U12.19 (~WR)
/~CS_FPU: U2.15 (IO5), U12.18 (~CS)
/~CS_IIC: U2.17 (I03), U8.17 (~CS)
/~CS_PIO: U2.16 (IO4), U6.4 (~CE)
/~CS_PS2: U2.18 (IO2), U9.6 (~INT)
/~IIC_WR: U2.14 (IO6), U8.18 (~WR)
/~INT0: J8.1, J10.b4 (~INT0), R14.1, U6.10 (PA4)
/~INT1: J8.3, J10.b5 (~INT1), R15.1, U6.9 (PA5)
/~INT2: J8.5, J10.b6 (~INT2), R16.1, U6.8 (PA6)
/~INT3: J8.7, J10.a6 (~INT3), R17.1, U6.7 (PA7)
/~INT_IIC: J2.3, R2.2, U8.5 (~INT)
/~INT_KB: R1.2, U6.13 (PA2), U7.10, U7.12
/~INT: J10.b17 (~INT), U6.23 (~INT)
/~IOREQ: J10.b25 (~IOREQ), U5.15 (B3)
/~M1: J10.b19 (~M1), U5.12 (B6)
/~RD: J10.b22 (~RD), U5.18 (B0)
/~RESET: J10.b15 (~RESET), U5.11 (B7)
/~RST_IIC: J2.6, U8.19 (~RST)
/~WAIT: J7.1 (A), J10.b20 (~WAIT)
/~WR: J10.b23 (~WR), U5.17 (B1)
BUSDIR: U2.12 (IO8), U3.1 (A->B)
GND: BT1.neg, C1.2, C2.2, C3.2, C4.2, C5.2, C6.2, C7.2, C8.2, C9.2, C10.2, C11.2, C12.2, C13.2, C14.2, C15.2, C16.2, D1.2 (A), D2.2 (A), D3.2 (A), D4.2 (A), D5.2 (A), D6.2 (A), D7.2 (A), D8.2 (A), J4.1, J4.13, J4.14, J5.3, J5.G, J6.3, J6.G, J10.G (CHASSIS), J10.a1 (GND), J10.a2 (GND), J10.a3 (GND), J10.a4 (GND), J10.b32 (GND), Q1.3 (E), RN1.1 (common), U1.1 (G), U1.10 (GND), U2.10 (GND), U3.10 (GND), U3.19 (CE), U4.1 (A->B), U4.10 (GND), U4.19 (CE), U5.1 (A->B), U5.10 (GND), U5.14 (B4), U5.16 (B2), U5.19 (CE), U6.11 (GND), U7.7 (GND), U8.10 (VSS), U9.2 (X1), U9.7 (EA), U9.20 (GND), U10.4 (GND), U11.3 (D0), U11.4 (D1), U11.5 (D2), U11.6 (D3), U11.8 (GND), U11.10 (CET), U12.1 (GND)
KBCI: C4.1, J6.5, U7.8, U9.1 (T0)
KBCO: U7.9, U9.37 (P2.6)
KBDI: C3.1, J6.1, U7.6, U9.27 (P1.0)
KBDO: U7.5, U9.38 (P2.7)
MSCI: C2.1, J5.5, U7.2, U9.39 (T1)
MSCO: U7.1, U9.24 (P2.3)
MSDI: C1.1, J5.1, U7.4, U9.28 (P1.1)
MSDO: U7.3, U9.23 (P2.2)
unnamed: D1.1 (K), R4.1, U6.27 (PB0)
unnamed: D2.1 (K), R5.1, U6.28 (PB1)
unnamed: D3.1 (K), R6.1, U6.29 (PB2)
unnamed: D4.1 (K), R7.1, U6.30 (PB3)
unnamed: D5.1 (K), R11.1, U6.34 (PB7)
unnamed: D6.1 (K), R12.1, U6.33 (PB6)
unnamed: D7.1 (K), R13.1, U6.32 (PB5)
unnamed: D8.1 (K), R10.1, U6.31 (PB4)
unnamed: J1.4, RN1.5 (R4), U1.12 (R4)
unnamed: J1.6, RN1.4 (R3), U1.14 (R5)
unnamed: J1.8, RN1.3 (R2), U1.16 (R6)
unnamed: J1.10, RN1.2 (R1), U1.18 (R7)
unnamed: J7.2 (B), U12.17 (~PAUSE)
unnamed: J8.2, J8.4, J8.6, J8.8, R19.2, U12.24 (~END)
unnamed: J9.1, U11.14 (Q0)
unnamed: J9.3, U11.13 (Q1)
unnamed: J9.5, U11.12 (Q2)
unnamed: J9.7, U11.11 (Q3)
unnamed: J10.b26 (IEI), U6.24 (IEI)
unnamed: J10.b27 (IEO), U6.22 (IEO)
unnamed: Q1.2 (B), R3.2
unnamed: LS1.2, Q1.1 (C)
unnamed: RN1.6 (R5), U1.9 (R3)
unnamed: RN1.7 (R6), U1.7 (R2)
unnamed: RN1.8 (R7), U1.5 (R1)
unnamed: RN1.9 (R8), U1.3 (R0)
unnamed: U1.19 (P=R), U2.8 (I8)
unnamed: U7.11, U9.35 (P2.4)
unnamed: U7.13, U9.36 (P2.5)
unnamed: BT1.pos, U10.3 (VBAT)
unnamed: U10.1 (X1), Y1.2
unnamed: U10.2 (X2), Y1.1
unnamed: R18.2, U12.3 (~EACK)
unnamed: R20.2, U12.4 (~SVACK)
